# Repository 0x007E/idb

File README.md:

# `IDB` - Inverter Development Board

The `IDB` is a board with an [CD40106](#additional-information) or any other 6-channel inverter that meets the pin requirements. The board itself can be driven from `5` to `15V`. The board offers the possibility to invert signals from buttons, switches or any other logic board.

| Experience  | Level                                                                               |
|:------------|:-----------------------------------------------------------------------------------:|
| Soldering   |  |

# Downloads

| Type      | File                                                                                                                                                 | Description     |
|:---------:|:----------------------------------------------------------------------------------------------------------------------------------------------------:|:----------------|
| Schematic | [pdf](https://github.com/0x007E/idb/releases/latest/download/schematic.pdf) / [cadlab](https://cadlab.io/project/30124/main/files)                   | Schematic files |
| Board     | [pdf](https://github.com/0x007E/idb/releases/latest/download/pcb.pdf) / [cadlab](https://cadlab.io/project/30124/main/files)                         | Board file      |
| Drill     | [pdf](https://github.com/0x007E/idb/releases/latest/download/drill.pdf)                                                                              | Drill file      |
| BoM | [xlsx](https://github.com/0x007E/idb/releases/latest/download/bom.xlsx) / [html](https://github.com/0x007E/idb/releases/latest/download/bom.html)          | Bill of Material as Excel/interactive HTML |
| PCB    | [zip](https://github.com/0x007E/idb/releases/latest/download/kicad.zip) / [tar](https://github.com/0x007E/idb/releases/latest/download/kicad.tar.gz)    | KiCAD/Gerber/BoM/Drill files       |
| Mechanical | [zip](https://github.com/0x007E/idb/releases/latest/download/freecad.zip) / [tar](https://github.com/0x007E/idb/releases/latest/download/freecad.tar.gz) | FreeCAD/Housing and PCB (STEP/STL) files     |

# Hardware

The pcb is created with `KiCAD`. All files are built with `github actions` so that they are ready for a production environment.

## PCB

The circuit board is populated on both sides (Top, Bottom). The best way for soldering the `SMD` components is within a vapor phase soldering system and for the `THT` components with a standard soldering system.

### Top Layer

### Bottom Layer

# Additional Information

| Type       | Link                                                  | Description                                 |
|:----------:|:-----------------------------------------------------:|:--------------------------------------------|
| CD40106    | [pdf](https://www.ti.com/lit/ds/symlink/cd40106b.pdf) | CD40106B CMOS Hex Schmitt-Trigger Inverters |

---

R. GAECHTER

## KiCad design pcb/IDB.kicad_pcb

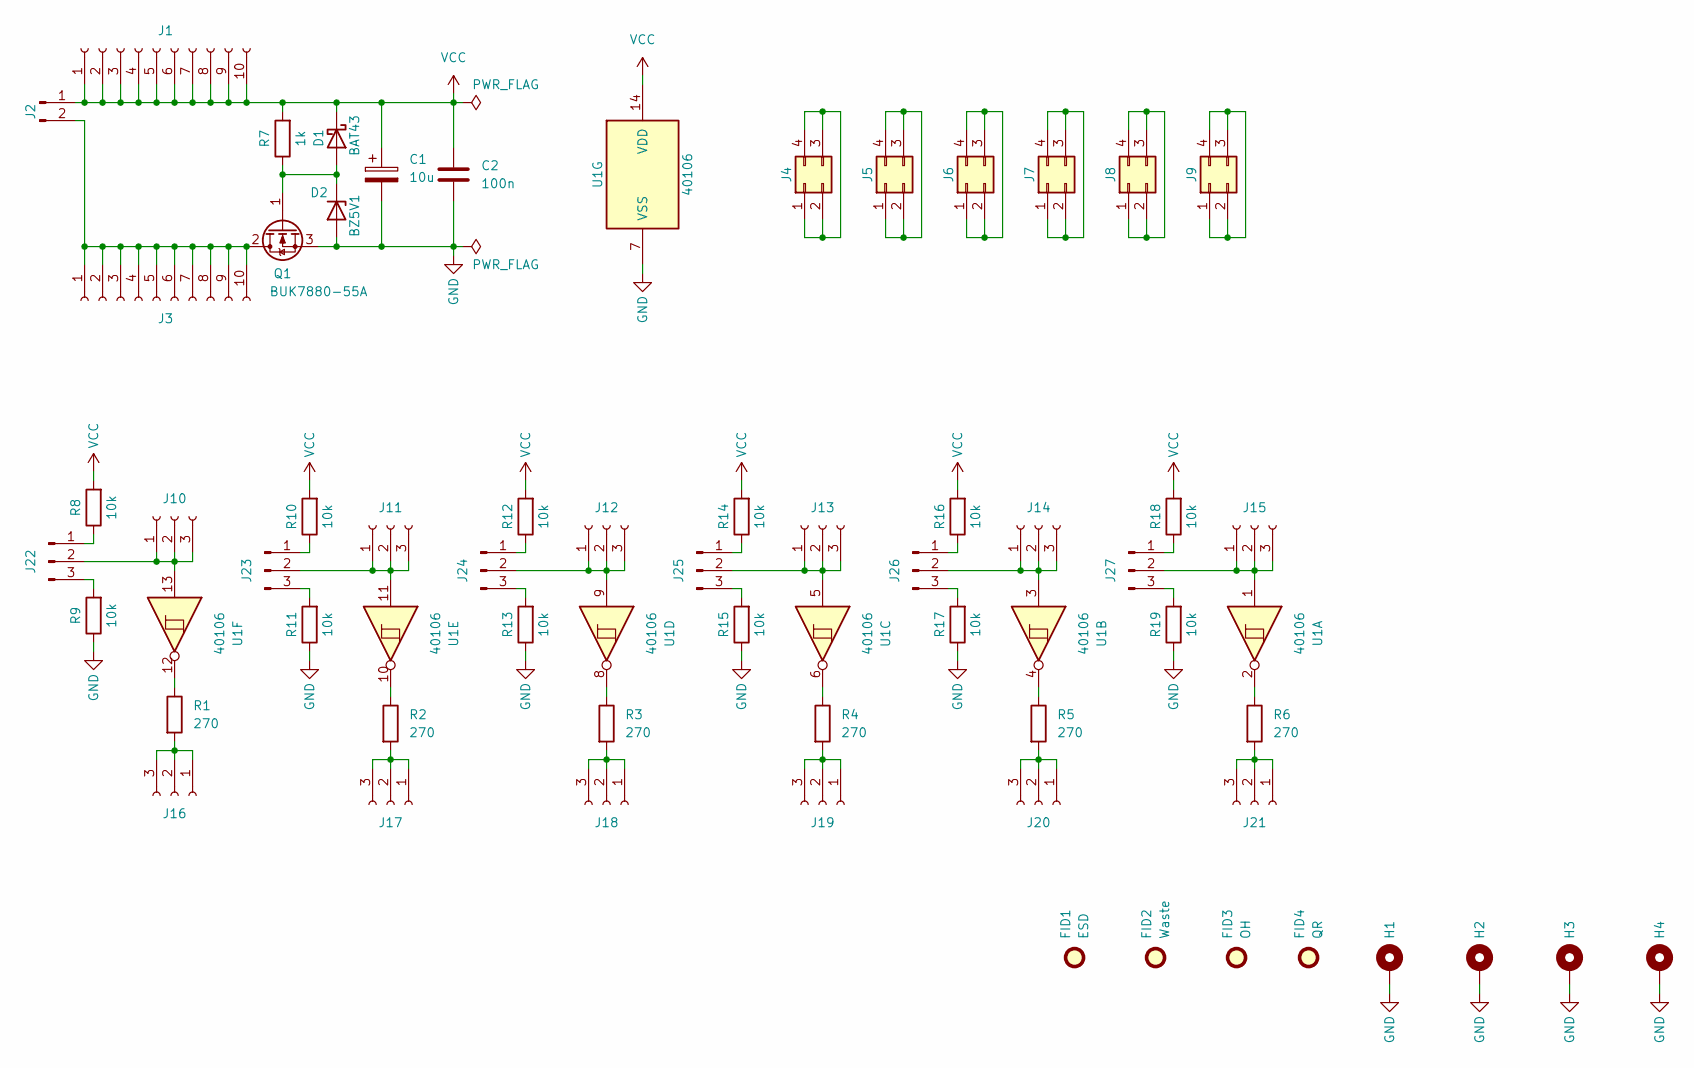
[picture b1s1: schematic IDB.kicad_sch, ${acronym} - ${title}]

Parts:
C1: 10u; CP_Radial_D6.3mm_P2.50mm
C2: 100n; C_1206_3216Metric
D1: BAT43; D_MiniMELF
D2: BZ5V1; D_MiniMELF
FID1: ESD; ESD-Logo_6.6x6mm_SilkScreen
FID2: Waste; WEEE-Logo_4.2x6mm_SilkScreen
FID3: OH; OSHW-Logo_5.7x6mm_SilkScreen
FID4: QR; QR_0x007e
H1, H2, H3, H4: MountingHole_Pad; MountingHole_3.2mm_M3_Pad
J1, J3: Conn_01x10_Socket; PinSocket_1x10_P2.54mm_Vertical; DigiKey 2057-RS1-10-G-ND
J2: Conn_01x02_Pin; PinHeader_1x02_P2.54mm_Vertical
J4, J5, J6, J7, J8, J9: Conn_02x02_Counter_Clockwise; PinSocket_2x02_P2.54mm_Vertical; DigiKey 2057-RS2-04-G-ND
J10, J11, J12, J13, J14, J15, J16, J17, J18, J19, J20, J21: Conn_01x03_Socket; PinSocket_1x03_P2.54mm_Vertical; DigiKey 2057-RS1-03-G-ND
J22, J23, J24, J25, J26, J27: Conn_01x03_Pin; PinHeader_1x03_P2.54mm_Vertical
Q1: BUK7880-55A; SOT-223-3_TabPin2
R1, R2, R3, R4, R5, R6: 270; R_1206_3216Metric
R7: 1k; R_1206_3216Metric
R8, R9, R10, R11, R12, R13, R14, R15, R16, R17, R18, R19: 10k; R_1206_3216Metric
U1: 40106; SOIC-14_3.9x8.7mm_P1.27mm; DigiKey 296-14081-1-ND

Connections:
GND: C1.2, C2.2, D2.2 (A), H1.1, H2.1, H3.1, H4.1, Q1.3 (S), R9.1, R11.1, R13.1, R15.1, R17.1, R19.1, U1.7 (VSS)
unnamed: D1.2 (A), D2.1 (K), Q1.1 (G), R7.1
unnamed: J2.2, J3.1, J3.2, J3.3, J3.4, J3.5, J3.6, J3.7, J3.8, J3.9, J3.10, Q1.2 (D)
unnamed: J4.1, J4.2, J4.3, J4.4
unnamed: J5.1, J5.2, J5.3, J5.4
unnamed: J6.1, J6.2, J6.3, J6.4
unnamed: J7.1, J7.2, J7.3, J7.4
unnamed: J8.1, J8.2, J8.3, J8.4
unnamed: J9.1, J9.2, J9.3, J9.4
unnamed: J10.1, J10.2, J10.3, J22.2, U1.13
unnamed: J11.1, J11.2, J11.3, J23.2, U1.11
unnamed: J12.1, J12.2, J12.3, J24.2, U1.9
unnamed: J13.1, J13.2, J13.3, J25.2, U1.5
unnamed: J14.1, J14.2, J14.3, J26.2, U1.3
unnamed: J15.1, J15.2, J15.3, J27.2, U1.1
unnamed: J16.1, J16.2, J16.3, R1.2
unnamed: J17.1, J17.2, J17.3, R2.2
unnamed: J18.1, J18.2, J18.3, R3.2
unnamed: J19.1, J19.2, J19.3, R4.2
unnamed: J20.1, J20.2, J20.3, R5.2
unnamed: J21.1, J21.2, J21.3, R6.2
unnamed: J22.1, R8.1
unnamed: J22.3, R9.2
unnamed: J23.1, R10.1
unnamed: J23.3, R11.2
unnamed: J24.1, R12.1
unnamed: J24.3, R13.2
unnamed: J25.1, R14.1
unnamed: J25.3, R15.2
unnamed: J26.1, R16.1
unnamed: J26.3, R17.2
unnamed: J27.1, R18.1
unnamed: J27.3, R19.2
unnamed: R1.1, U1.12
unnamed: R2.1, U1.10
unnamed: R3.1, U1.8
unnamed: R4.1, U1.6
unnamed: R5.1, U1.4
unnamed: R6.1, U1.2
VCC: C1.1, C2.1, D1.1 (K), J1.1, J1.2, J1.3, J1.4, J1.5, J1.6, J1.7, J1.8, J1.9, J1.10, J2.1, R7.2, R8.2, R10.2, R12.2, R14.2, R16.2, R18.2, U1.14 (VDD)

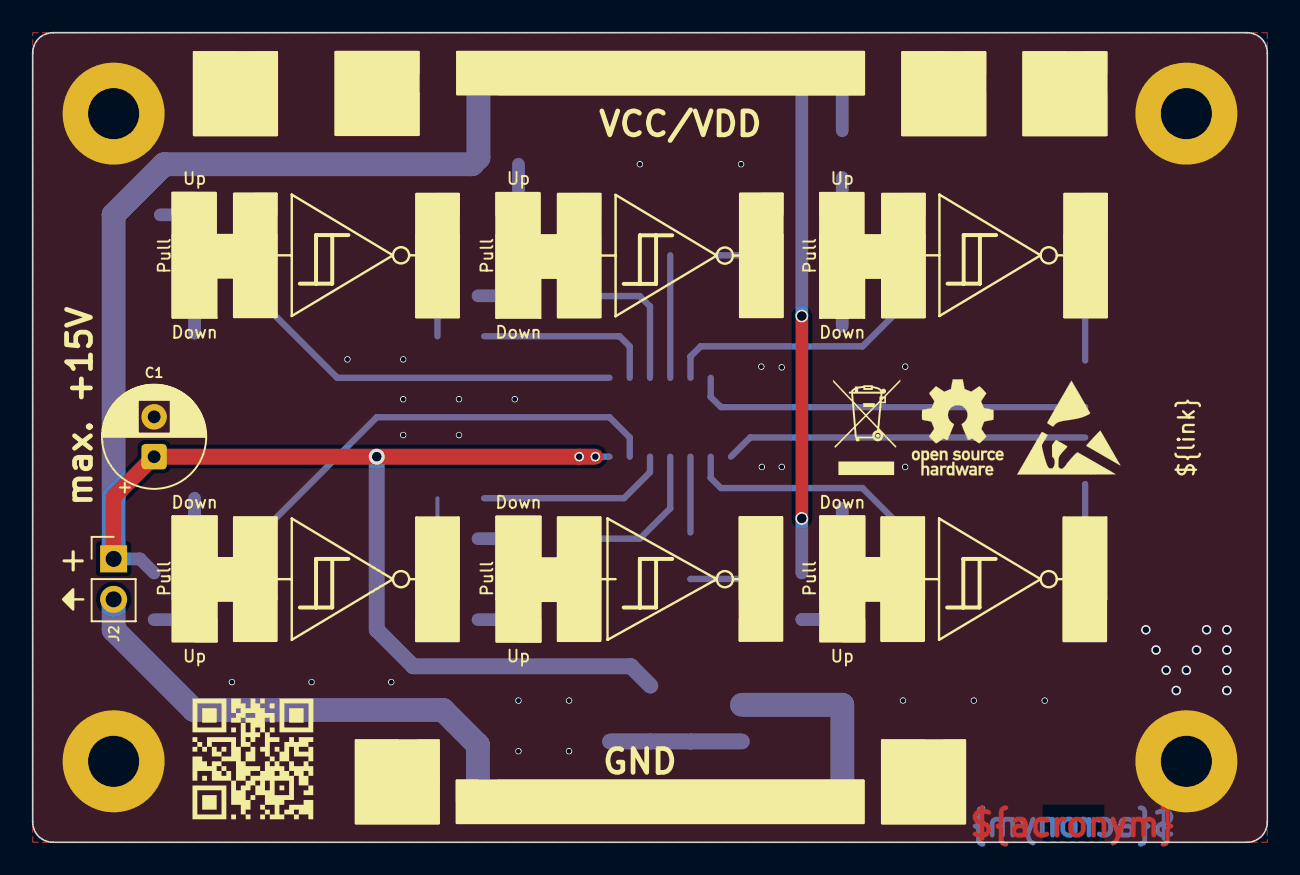
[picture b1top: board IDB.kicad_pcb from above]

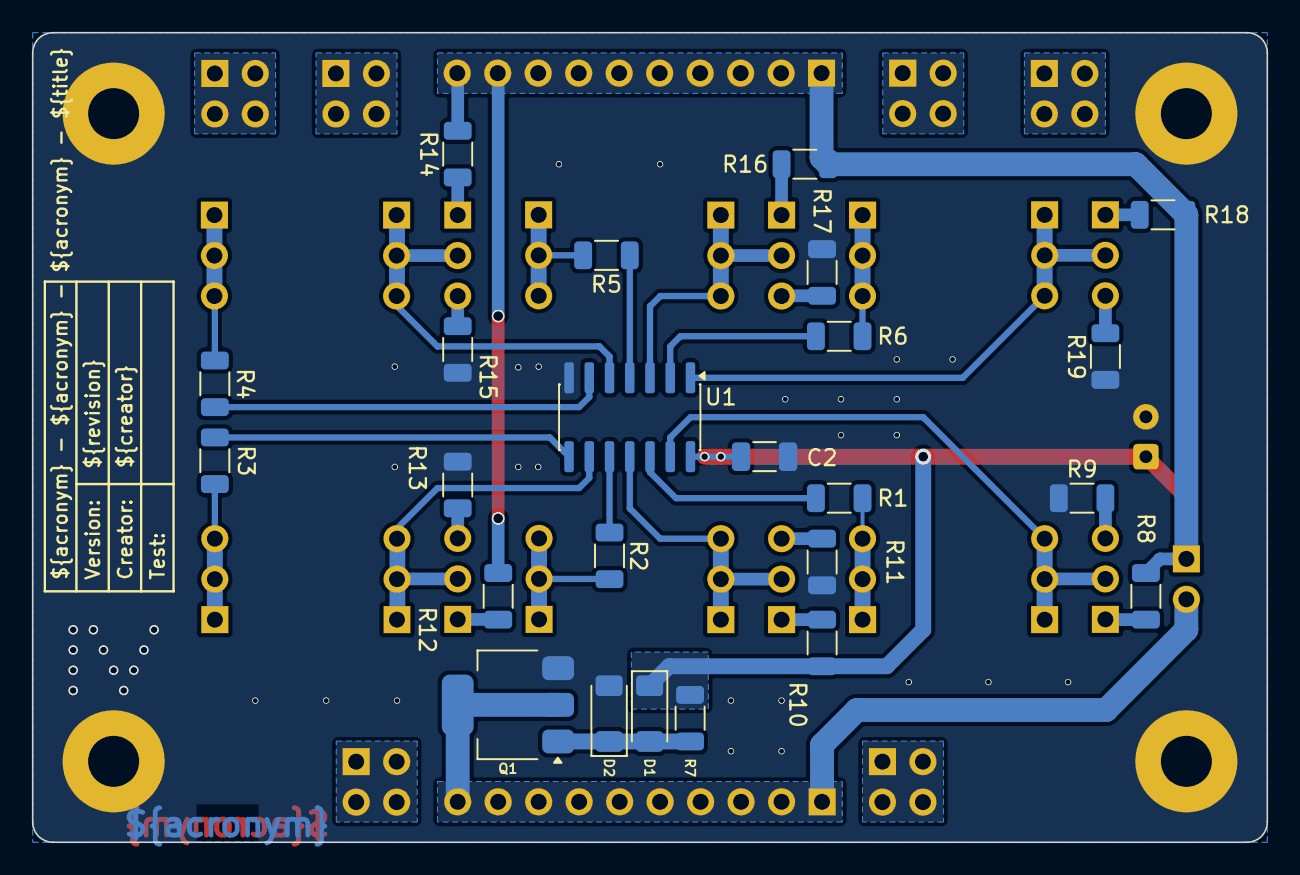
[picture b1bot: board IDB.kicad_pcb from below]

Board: 2 copper layers, 77.5 x 50.8 mm, 60 parts (24 on the bottom side), 40 nets.

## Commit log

2026-03-02 Add pcb layout
2026-03-02 Add README.md
2026-03-02 Add build pipeline
2026-03-02 Add release pipeline
2026-03-02 Fix wrong cadlab link
2026-03-09 Remove invalid text
2026-03-23 Adapt edge cuts and dimensioning
2026-03-23 Add FreeCAD modification and export
2026-03-23 Add mechanical download link
2026-05-09 Add reverse polarity protection
2026-05-09 Remove isolated copper filter
2026-05-11 Optimize fabrication layer
2026-05-12 Adapt description
2026-05-28 Add missing inversion at silkscreen
2026-05-29 Add push/pull possibility for inputs
2026-05-29 Update to KiCAD 9
2026-05-29 Rename/Add/Remove bom fields
2026-05-29 Add extended links to download section
2026-05-29 Optimize/Extend build pipeline
2026-05-29 Optimize/Extend release pipeline
2026-05-29 Optimize silkscreen

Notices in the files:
README.md:
License CC By-NC-SA
parts and their libraries:
license: CC BY-NC-SA 4.0
